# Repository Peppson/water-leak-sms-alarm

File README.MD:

# water-leak-sms-alarm   
A small battery-powered device that detects water leakage and sends an SMS alert.  
&nbsp;

&nbsp; 
## Features
- Completely `off` until water *(or anything conductive)* closes the circuit between two of its legs,  
thereby latching on the "soft latching power circuit".  
Which can later be turned off again by the microcontroller.

- Latches `on` by either water detection or by pressing the test button.

- Sends an SMS alert if water is detected.

- Sends SMS diagnostics if the test button is pressed.

- Built with an ESP32 and PlatformIO, in C++.

&nbsp; 
## Schematic and PCB
KiCad files can be found here: 
[📂 _KiCad/](./_KiCad/)  
More images in: 
[📂 _images/](./_images/)
<details>
    <summary>
        Parts used
    </summary>   

- ESP32 D1 Mini Node MCU 
- SIM800L module with external antenna  
- 3.3V LDO: MCP1700-3302E (250mA)
- LED: WS2812B  
- P-channel mos: NTR4101PT1G 
- N-channel mos: PMV16XNR  
- Cap 470uF: Electrolytic  
- Cap 22uF: Electrolytic
- Cap 1uF: Ceramic  
- Cap 100nF: Ceramic
- Switch: Momentary DPST  
- Conductive legs in copper/brass  
</details>

<details>
    <summary>
        PCB
    </summary>   

> Uses mostly through-hole components for easier soldering.  
> ESP32 is mounted on the bottom side of the PCB.

&nbsp;
</details>

### Schematic

### SMS Example

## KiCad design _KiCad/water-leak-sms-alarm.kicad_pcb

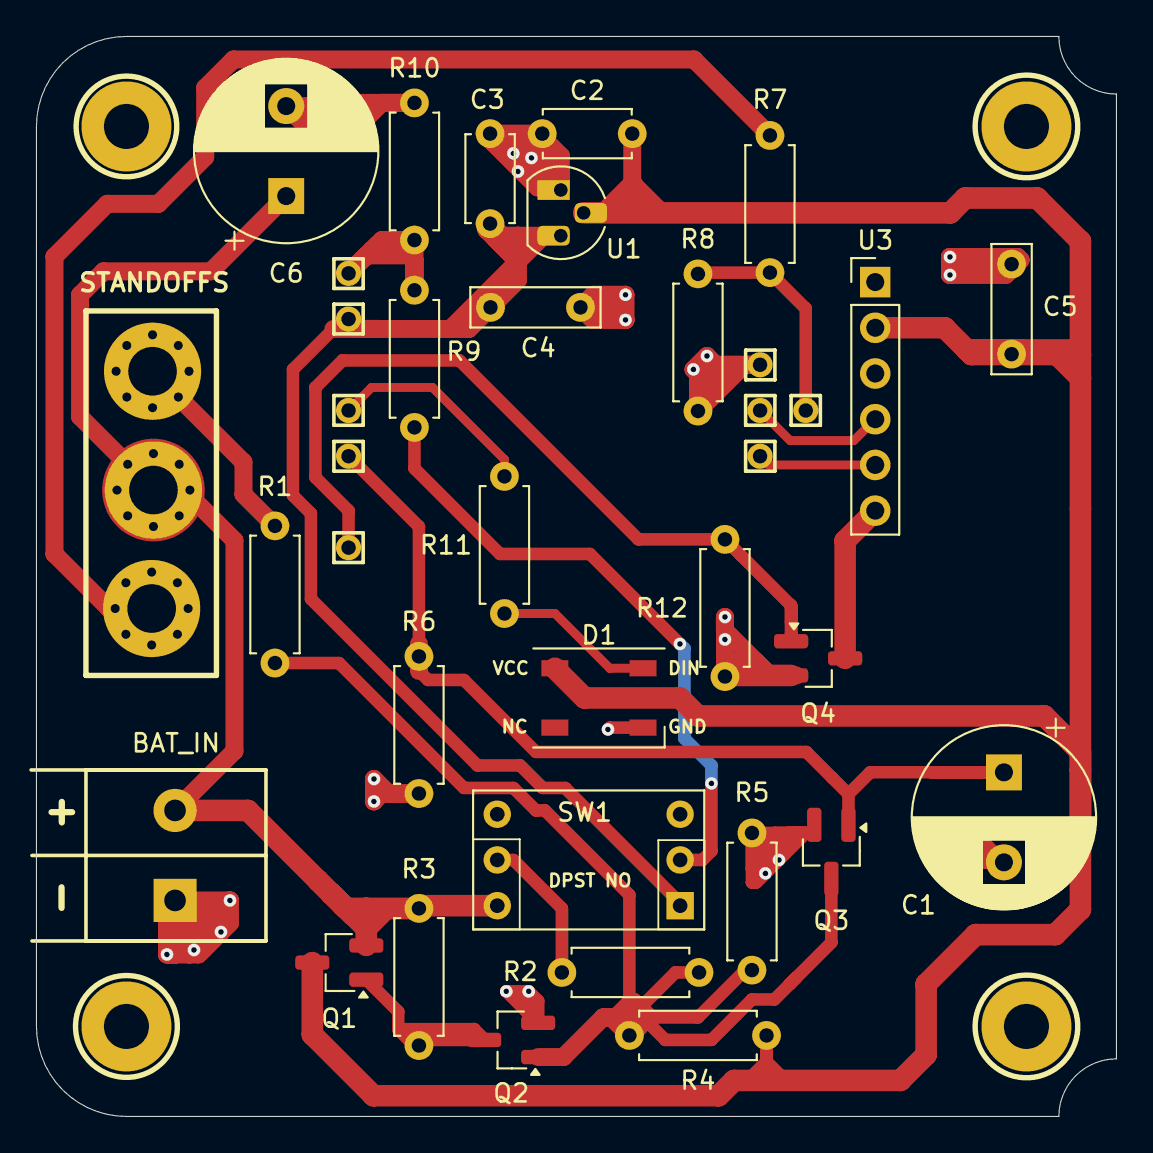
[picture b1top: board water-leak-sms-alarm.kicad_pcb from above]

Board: 2 copper layers, 60.0 x 60.0 mm, 35 parts (1 on the bottom side), 19 nets.

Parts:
BAT_IN: Screw_Terminal_01x02; TerminalBlock_Philmore_TB132_1x02_P5.00mm_Horizontal
C1: 470uF; CP_Radial_D10.0mm_P5.00mm
C2, C3: 1uF; C_Disc_D4.7mm_W2.5mm_P5.00mm
C4, C5: C_Rect_L7.0mm_W2.0mm_P5.00mm
C6: 470; CP_Radial_D10.0mm_P5.00mm
D1: WS2812B; LED_WS2812B_PLCC4_5.0x5.0mm_P3.2mm
H1, H2, H3, H4: MountingHole; MountingHole_2.5mm_Pad
Q1: NTR4101PT1G; SOT-23_Handsoldering
Q2, Q3, Q4: PMV16XNR; SOT-23_Handsoldering
R1, R2, R7: 330; R_Axial_DIN0207_L6.3mm_D2.5mm_P7.62mm_Horizontal
R3, R4, R6: 100K; R_Axial_DIN0207_L6.3mm_D2.5mm_P7.62mm_Horizontal
R5: 300K; R_Axial_DIN0207_L6.3mm_D2.5mm_P7.62mm_Horizontal
R8: 680; R_Axial_DIN0207_L6.3mm_D2.5mm_P7.62mm_Horizontal
R9: 150; R_Axial_DIN0207_L6.3mm_D2.5mm_P7.62mm_Horizontal
R10, R12: 10K; R_Axial_DIN0207_L6.3mm_D2.5mm_P7.62mm_Horizontal
R11: 270; R_Axial_DIN0207_L6.3mm_D2.5mm_P7.62mm_Horizontal
S1: CUNDUCTIVE_LEGS (legs 0, 1); MountingHole_2.7mm_M2.5_Pad_Via
S2: CUNDUCTIVE STANDOFFS (legs 1, 2); MountingHole_2.7mm_M2.5_Pad_Via
S3: CUNDUCTIVE_LEG (leg 2); MountingHole_2.7mm_M2.5_Pad_Via
SW1: TEST; SW_NKK_G1xJP
U1: MCP1700x-120xxTO; TO-92_HandSolder
U2: mini_esp32; esp32-wemos-d1-mini
U3: SIM800L-CORE; PinHeader_1x06_P2.54mm_Vertical

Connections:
+3.3V: C3.1, C4.2, SW1.1, U1.3 (VO), U2.16 (3V3)
CIRCUIT_POWER_SWITCH: C1.1, Q3.1 (D), R6.2, U2.10 (IO_19/D6)
GND: BAT_IN.1, C1.2, C2.2, C3.2, C4.1, C5.1, C6.2, D1.3 (GND), Q2.2 (G), Q3.2 (G), Q4.2 (G), R5.1, R6.1, R8.1, R10.1, R12.1, U1.1 (GND), U2.33 (GND)
unnamed: D1.4 (DIN), R11.2
unnamed: BAT_IN.2, C6.1, Q1.2 (G), R3.2, S1.1, SW1.3
unnamed: Q1.1 (D), Q2.3 (S), R3.1
unnamed: Q2.1 (D), Q3.3 (S), R1.1, R2.1, R4.1, R5.2
unnamed: Q4.3 (S), U3.6 (GND)
unnamed: R1.2, S2.1
unnamed: R2.2, SW1.4
unnamed: R7.2, S3.1
unnamed: R7.1, R8.2, U2.32 (IO_04)
unnamed: R9.2, R10.2, U2.18 (IO_13/TCK)
unnamed: R11.1, U2.12 (IO_23/D7)
SERIAL_RX: U2.29 (IO_17/D3), U3.5 (TXD)
SERIAL_TX: U2.31 (IO_16/D4), U3.4 (RXD)
SIM800L_POWER_SWITCH: Q4.1 (D), R12.2, U2.6 (IO_26/D0)
TEST_BUTTON: R9.1, SW1.2
VCC_4.5V: C2.1, C5.2, D1.1 (VCC), Q1.3 (S), R4.2, U1.2 (VI), U3.2 (VCC)

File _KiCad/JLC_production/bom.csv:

Designator,Footprint,Quantity,Value,LCSC Part #
BAT_IN,TerminalBlock_Philmore_TB132_1x02_P5.00mm_Horizontal,1,Screw_Terminal_01x02,
"C1, C5",CP_Radial_D10.0mm_P5.00mm,2,470uF,
"C2, C3",C_Disc_D4.7mm_W2.5mm_P5.00mm,2,1uF,
C4,CP_Radial_D10.0mm_P5.00mm,1,470,
C6,C_Rect_L7.0mm_W2.0mm_P5.00mm,1,C_Rect_L7.0mm_W2.0mm_P5.00mm,
D1,LED_WS2812B_PLCC4_5.0x5.0mm_P3.2mm,1,WS2812B,
Q1,SOT-23_Handsoldering,1,NTR4101PT1G ,
"Q2, Q3, Q4",SOT-23_Handsoldering,3,PMV16XNR ,
"R1, R2, R7",R_Axial_DIN0207_L6.3mm_D2.5mm_P7.62mm_Horizontal,3,330,
"R10, R12",R_Axial_DIN0207_L6.3mm_D2.5mm_P7.62mm_Horizontal,2,10K,
R11,R_Axial_DIN0207_L6.3mm_D2.5mm_P7.62mm_Horizontal,1,270,
"R3, R4, R6",R_Axial_DIN0207_L6.3mm_D2.5mm_P7.62mm_Horizontal,3,100K,
R5,R_Axial_DIN0207_L6.3mm_D2.5mm_P7.62mm_Horizontal,1,300K,
R8,R_Axial_DIN0207_L6.3mm_D2.5mm_P7.62mm_Horizontal,1,680,
R9,R_Axial_DIN0207_L6.3mm_D2.5mm_P7.62mm_Horizontal,1,150,
S1,MountingHole_2.7mm_M2.5_Pad_Via,1,"CUNDUCTIVE_LEGS (legs 0, 1)",
S2,MountingHole_2.7mm_M2.5_Pad_Via,1,"CUNDUCTIVE STANDOFFS (legs 1, 2)",
S3,MountingHole_2.7mm_M2.5_Pad_Via,1,CUNDUCTIVE_LEG (leg 2),
SW1,SW_NKK_G1xJP,1,TEST,
U1,TO-92_HandSolder,1,MCP1700x-120xxTO,
U2,esp32-wemos-d1-mini,1,mini_esp32,
U3,PinHeader_1x06_P2.54mm_Vertical,1,SIM800L-CORE,

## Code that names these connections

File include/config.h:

#pragma once
#include <Arduino.h>
#include <stdbool.h>
#include <stdexcept>
#include <stdio.h>
#include <string>
#include <EEPROM.h>


// Dev
#define SEND_SMS_ENABLED 1                                          // SMS toggle 
#define USB_SERIAL_ENABLED 0                                        // USB serial connection toggle
#define DEBUG_LOOP_ENABLED 0                                        // Enter debug loop
#define DEBUG_LOOP_PING 0                                           // Serial print (".") while in debug_loop, sometimes helps with connection     
#define RESET_ALL 0                                                 // Resets all counters and await new code upload   

// Setup
constexpr const char* SMS_ALERT_ROW_0 = "WARNING!";                 // Alert sms first row
constexpr const char* SMS_ALERT_ROW_1 = "Water leak detected!";     // Alert sms second row
constexpr const char* SMS_DIAGNOSTIC_ROW_0 = "Status!";             // Diagnostic sms first row
constexpr uint32_t CONNECTION_TIMEOUT = 45*1000;                    // Wait for GSM network connection (mS)
constexpr uint32_t DEEPSLEEP_DURATION_LONG = 2*60*60;               // Deepsleep after waterleak is detected (S)
constexpr uint32_t DEEPSLEEP_DURATION_SHORT = 10;                   // Deepsleep after false positive (S)
constexpr uint16_t SERIAL_RESPONSE_TIMEOUT = 75;                    // Wait for serial response from SIM800L (mS)
constexpr uint16_t MAX_SMS_UNTILL_EMPTY_SIMCARD = 50;               // How many sms can we send in total? (money/sms cost)
constexpr uint64_t DEEPSLEEP_uS_TO_S_FACTOR = 1000000;              // Factor

// Physical I/O
#define PIN_CIRCUIT_POWER_SWITCH 19                                 // Pull HIGH to turn off ALL power (latching circuit)
#define PIN_SIM800L_POWER_SWITCH 26                                 // Turn on/off power to the SIM800L module 
#define PIN_TEST_BUTTON 13                                          // Input push button
#define PIN_WATERLEAK_DETECT 4                                      // Input (third conductive leg) to detect water leakage
#define PIN_LED 23                                                  // Datapin WS2812B led (SPI MOSI)
#define PIN_SIM800L_RX 17                                           // ESP32 hardware serial 2 RX
#define PIN_SIM800L_TX 16                                           // ESP32 hardware serial 2 TX

// Print toggle
#if USB_SERIAL_ENABLED
    #define log(...) Serial.printf(__VA_ARGS__)
    #define STOP log("\n-----  Stop right there criminal scum!  ----- \n"); while (1) { delay(1); }
#else
    #define log(...)
    #define STOP
#endif

// Enums
enum class SMSType : uint8_t {
    Alert,
    Diagnostic,
    None
};

enum class Color : uint8_t {
    Orange,
    Green,
    Blue,
    Red,
    Off
};

enum MemAddr : int {
    BootCount,
    SmsSent,
    NumOfMemAddr  // Num of items. Well, it only grew to two
};

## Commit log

2024-04-30 public
